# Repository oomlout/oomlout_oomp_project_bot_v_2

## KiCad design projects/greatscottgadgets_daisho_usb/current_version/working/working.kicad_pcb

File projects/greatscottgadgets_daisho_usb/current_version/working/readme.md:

# daisho
 
## summary 
* id: greatscottgadgets_daisho_usb
* user: greatscottgadgets
* name: daisho
* board: usb
* repo: https://github.com/greatscottgadgets/daisho
* src_file_repo_kicad_pcb: hw/frontend/usb/usb.kicad_pcb
* src_file_repo_kicad_pcb_link: https://github.com/greatscottgadgets/daisho/tree/master/hw/frontend/usb/usb.kicad_pcb

* src_file_repo_sch: 
* src_file_repo_sch_link: https://github.com/greatscottgadgets/daisho/tree/master/
* full details link: https://github.com/oomlout/oomlout_oomp_project_bot_v_2/tree/main/projects/greatscottgadgets_daisho_usb/current_version/working

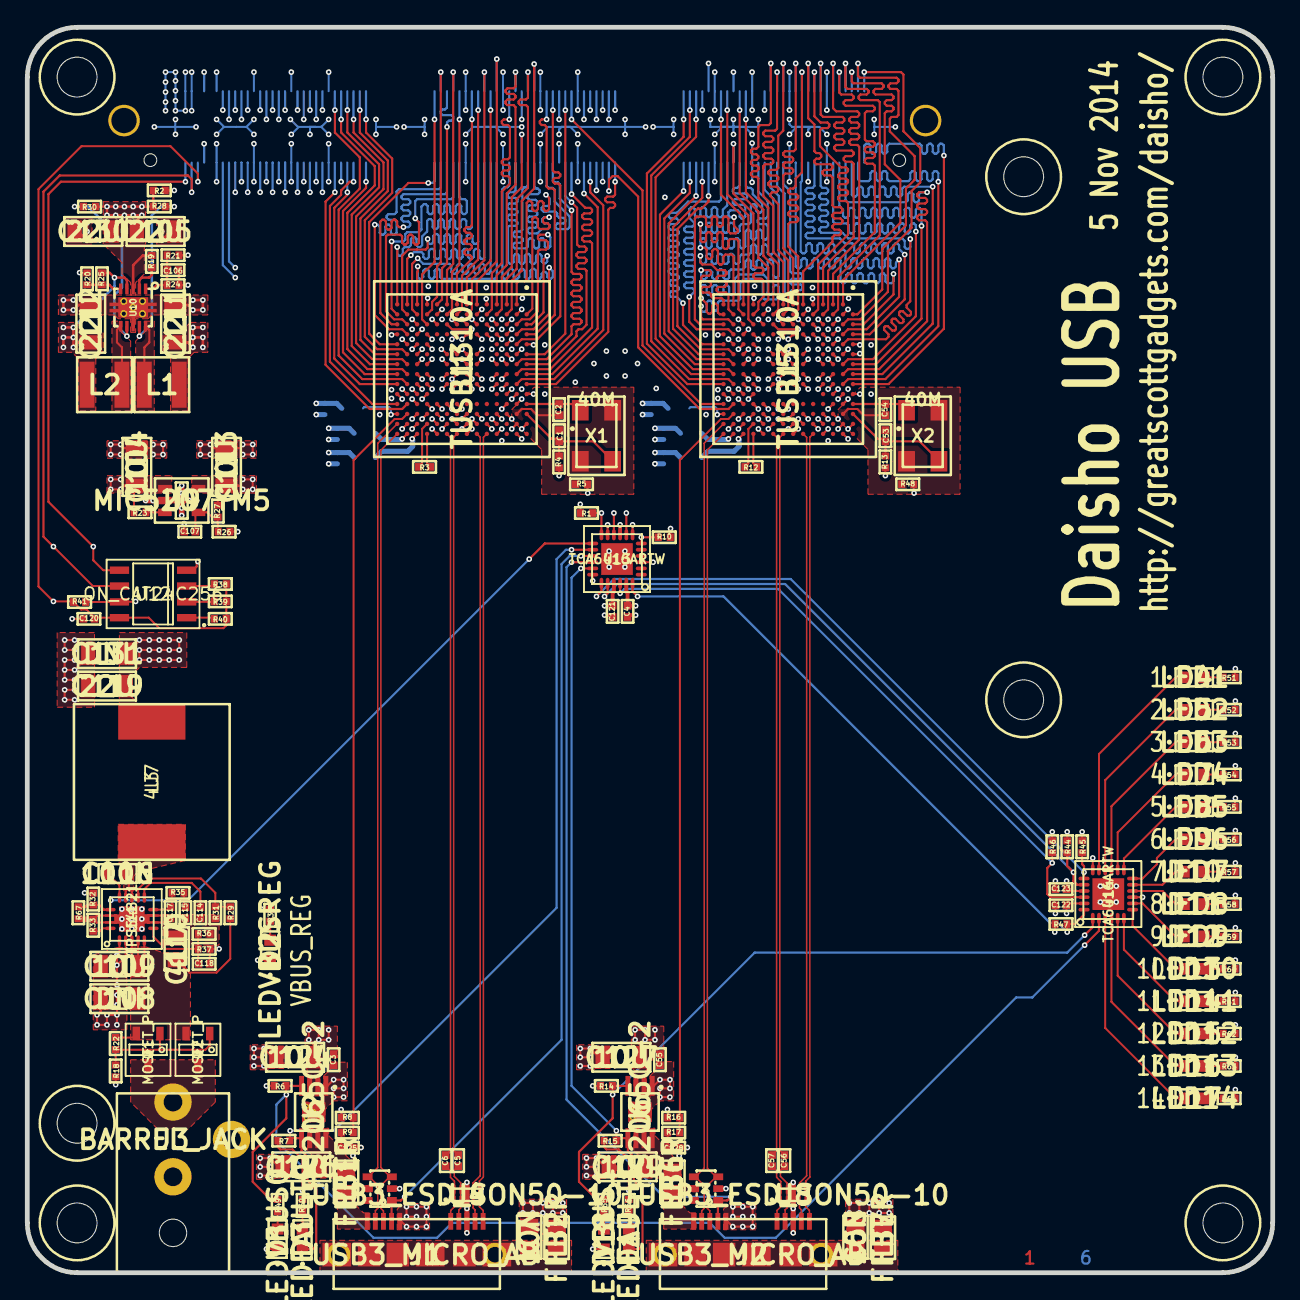
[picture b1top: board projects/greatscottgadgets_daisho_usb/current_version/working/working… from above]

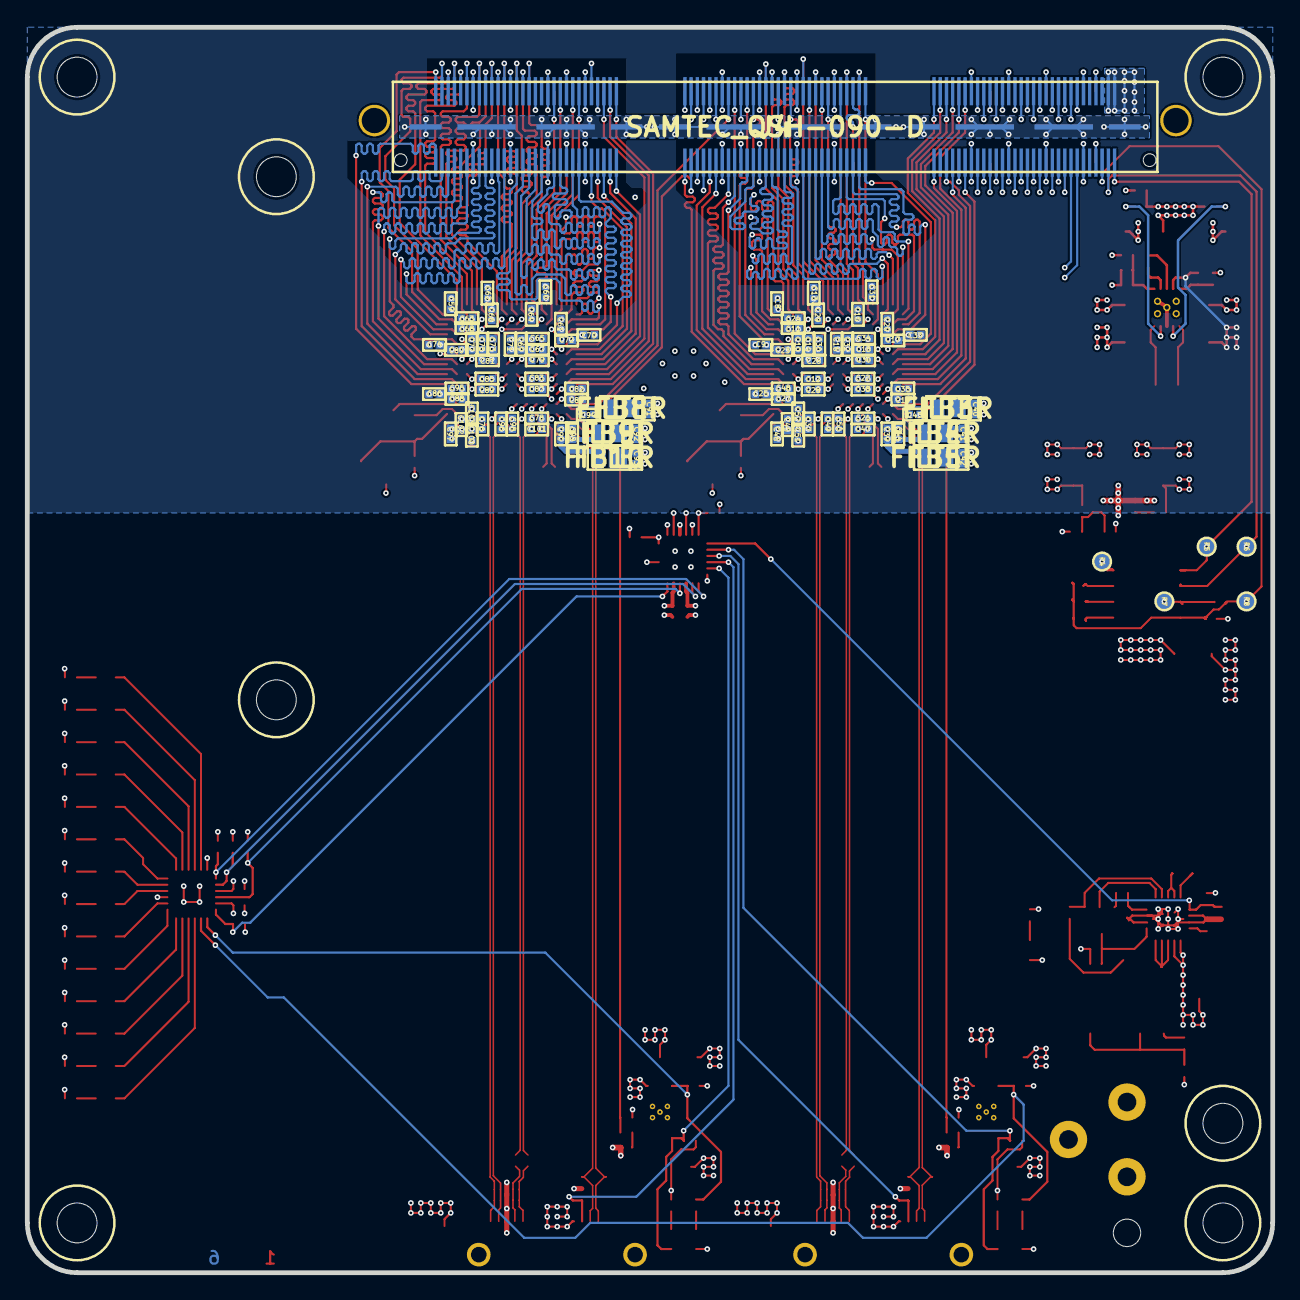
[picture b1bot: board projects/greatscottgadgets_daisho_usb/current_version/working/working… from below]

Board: 6 copper layers, 100.0 x 100.0 mm, 261 parts (109 on the bottom side), 265 nets.

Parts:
C1, C2, C53, C54: 27P; IPC_CAPC1005X55N
C3, C4, C5, C6, C8, C9, C10, C11, C12, C13, C14, C15, C16, C17, C18, C19, C20, C21, C22, C23, C24, C25, C26, C27, C28, C29, C30, C31, C32, C33, C34, C35, C36, C37, C38, C40, C41, C42, C43, C44, C45, C46, C47, C48, C49, C50, C51, C52, C55, C56, C57, C59, C60, C61, C62, C63, C64, C65, C66, C67, C68, C69, C70, C71, C72, C73, C74, C75, C76, C77, C78, C79, C80, C81, C82, C83, C84, C85, C86, C87, C88, C89, C91, C92, C93, C94, C95, C96, C97, C98, C99, C100, C101, C102, C103, C120, C121, C122, C123, C125, C128: 100N; IPC_CAPC1005X55N
C7, C58: 10N; IPC_CAPC2012X140N
C39, C90: 1U; IPC_CAPC1005X55N
C104, C109, C113, C124, C126, C127, C129: 10U; IPC_CAPC3216X180N
C105, C111, C112, C119, C130: 22U; IPC_CAPC3216X180N
C106: 33P; IPC_CAPC1005X55N
C107: 470P; IPC_CAPC1005X55N
C108, C131: DNI; IPC_CAPC3216X180N
C110: 4U7; IPC_CAPC2012X140N
C114: 22N; IPC_CAPC1005X55N
C115: 82N; IPC_CAPC1005X55N
C116: 100N; IPC_CAPC1608X90N
C117: 1N5; IPC_CAPC1005X55N
C118: 220P; IPC_CAPC1005X55N
D1: LEDVBUS0; IPC_LEDC1608X60N
D2: LEDVBUSREG; IPC_LEDC1608X60N
D3: LEDFAULT0; IPC_LEDC1608X60N
D4: LED1; IPC_LEDC1608X60N
D5: LED2; IPC_LEDC1608X60N
D6: LED3; IPC_LEDC1608X60N
D7: LED4; IPC_LEDC1608X60N
D8: LED5; IPC_LEDC1608X60N
D9: LED6; IPC_LEDC1608X60N
D10: LED7; IPC_LEDC1608X60N
D11: LED8; IPC_LEDC1608X60N
D12: LED9; IPC_LEDC1608X60N
D13: LED10; IPC_LEDC1608X60N
D14: LED11; IPC_LEDC1608X60N
D15: LED12; IPC_LEDC1608X60N
D16: LED13; IPC_LEDC1608X60N
D17: LED14; IPC_LEDC1608X60N
D18: LEDVBUS1; IPC_LEDC1608X60N
D19: LEDFAULT1; IPC_LEDC1608X60N
FB1, FB2, FB3, FB4, FB5, FB6, FB7, FB8, FB9, FB10: FILTER; IPC_INDC2012X130N
H1, H2, H4, H5, H6, H7, H8: HOLE; GSG-HOLE126MIL
J1, J2: USB3_MICRO_AB
J3: BARREL_JACK; CUI_PJ-102[AB]H
J4: SAMTEC_QSH-090-D; SAMTEC_QSH-090-01-F-D-A
L1, L2: 4U7; GSG-NRG4026
L3: 4U7; BOURNS_SRR1260
P4, P5, P6, P7, P8: CONN_1; GSG-TESTPOINT-50MIL
Q1, Q2: MOSFET_P; IPC_SOT95P280X125-3N_GSD
R1, R2, R3, R6, R7, R8, R10, R12, R14, R15, R16, R19, R44, R45, R46, R47: 10K; IPC_RESC1005X40N
R4, R5, R13, R38, R39, R40, R41, R48: DNI; IPC_RESC1005X40N
R9, R17: 90K9; IPC_RESC1005X40N
R18, R22: 30K; IPC_RESC1005X40N
R20: 165K; IPC_RESC1005X40N
R21: 180K; IPC_RESC1005X40N
R23, R28, R30: 0R; IPC_RESC1005X40N
R24: 360K; IPC_RESC1005X40N
R25: 137K; IPC_RESC1005X40N
R26: 174K; IPC_RESC1005X40N
R27: 105K; IPC_RESC1005X40N
R29: 22K; IPC_RESC1005X40N
R31: 9K53; IPC_RESC1005X40N
R32: 49K9; IPC_RESC1005X40N
R33: 52K3; IPC_RESC1005X40N
R34, R49, R50, R51, R52, R53, R54, R55, R56, R57, R58, R59, R60, R61, R62, R63, R64, R65, R66: 1K; IPC_RESC1005X40N
R35: 1K58; IPC_RESC1005X40N
R36: 2K21; IPC_RESC1005X40N
R37: 16K2; IPC_RESC1005X40N
R67: 1M; IPC_RESC1005X40N
U1, U5: TUSB1310A; IPC_BGA175C80P14X14_1200X1200X140
U2, U6: TPS2065C-2; TI_DGN_S-PDSO-G8
U3, U7: GSG-IP4220CZ6; GSG-SOT457
U4, U8: USB3_ESD_SON50-10
U9: MIC5207YM5; IPC_SOT95P280X110-5N
U10: TPS62420; TI_DRC_S-PVSON-N10
U11: TPS54821; TI_RHL_S-PVQFN-N14
U12: ON_CAT24C256; IPC_SOIC127P600X175-8N
U13, U14: TCA6416ARTW; ti_rtw_s-pwqfn-n24
X1, X2: 40M; IPC_OSCCC320X500X105-4N

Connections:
/main_board_if/EEPROM_A0: R40.1, U12.1
/main_board_if/EEPROM_A1: R39.1, U12.2
/main_board_if/EEPROM_A2: R38.1, U12.3
/main_board_if/EEPROM_VCC: C120.1, J4.6, P8.1, R38.2, R39.2, R40.2, R41.2, U12.8
/main_board_if/EEPROM_WP: P7.1, R41.1, U12.7
/main_board_if/FE_I2C_SCL: J4.4, P6.1, U12.6
/main_board_if/FE_I2C_SDA: J4.2, P5.1, U12.5
/main_board_if/IO_INT#: J4.14, R46.1, U13.22, U14.22
/main_board_if/IO_RESET#: J4.16, R47.2, U13.24, U14.24
/main_board_if/IO_SCL: J4.13, R45.1, U13.19, U14.19
/main_board_if/IO_SDA: J4.15, R44.1, U13.20, U14.20
/main_board_if/USB0_POWER_EN: R6.2, R49.2, U2.4, U14.2
/main_board_if/USB0_POWER_FLT#: D3.2, R7.2, U2.5, U13.14
/main_board_if/USB0_XI: J4.8, R4.2
/main_board_if/USB1_POWER_EN: R14.2, R65.2, U6.4, U14.1
/main_board_if/USB1_POWER_FLT#: D19.2, R15.2, U6.5, U13.17
/main_board_if/USB1_XI: J4.7, R13.2
/main_board_if/VALT_FE_PWRGD: R32.2, R67.2, U11.14, U13.13
/power/DC_IN: J3.1, Q1.D, Q2.D
/power/SW_PH: C116.2, L3.2, U11.11, U11.12
/power/SW_PVIN: C108.1, C109.1, C110.1, Q1.S, Q2.S, R22.2, R29.1, U11.4, U11.5, U11.6
/power/V1P1_FB: R20.1, R25.2, U10.5
/power/V1P1_SW: L2.1, U10.6
/power/V1P8_FB: C106.1, R21.1, R24.2, U10.1
/power/V1P8_SW: L1.2, U10.10
/usb0_interfaces/DM: J1.2, U1.P13, U3.4
/usb0_interfaces/DP: J1.3, U1.P14, U3.3
/usb0_interfaces/ELAS_BUF_MODE: J4.31, U1.C9
/usb0_interfaces/ID: J1.4, U3.1, U13.15
/usb0_interfaces/PCLK: J4.103, U1.A6
/usb0_interfaces/PHY_RESETN: U1.J3, U13.10
/usb0_interfaces/PHY_STATUS: J4.42, U1.E3
/usb0_interfaces/POWER_DOWN0: J4.46, U1.H3
/usb0_interfaces/POWER_DOWN1: J4.52, U1.G3
/usb0_interfaces/PWRPRESENT: J4.32, U1.H11
/usb0_interfaces/RESETN: R1.2, U1.J11, U13.12
/usb0_interfaces/RX_DATA0: J4.85, U1.E2
/usb0_interfaces/RX_DATA1: J4.90, U1.D2
/usb0_interfaces/RX_DATA2: J4.87, U1.D1
/usb0_interfaces/RX_DATA3: J4.91, U1.C1
/usb0_interfaces/RX_DATA4: J4.93, U1.C2
/usb0_interfaces/RX_DATA5: J4.98, U1.B1
/usb0_interfaces/RX_DATA6: J4.94, U1.A2
/usb0_interfaces/RX_DATA7: J4.88, U1.A3
/usb0_interfaces/RX_DATA8: J4.92, U1.B3
/usb0_interfaces/RX_DATA9: J4.97, U1.A4
/usb0_interfaces/RX_DATA10: J4.86, U1.B4
/usb0_interfaces/RX_DATA11: J4.99, U1.B5
/usb0_interfaces/RX_DATA12: J4.106, U1.B8
/usb0_interfaces/RX_DATA13: J4.110, U1.A8
/usb0_interfaces/RX_DATA14: J4.120, U1.A9
/usb0_interfaces/RX_DATA15: J4.112, U1.B9
/usb0_interfaces/RX_DATAK0: J4.104, U1.A7
/usb0_interfaces/RX_DATAK1: J4.100, U1.B7
/usb0_interfaces/RX_ELECIDLE: J4.17, U1.F3
/usb0_interfaces/RX_POLARITY: J4.29, U1.C8
/usb0_interfaces/RX_STATUS0: J4.21, U1.C5
/usb0_interfaces/RX_STATUS1: J4.25, U1.C6
/usb0_interfaces/RX_STATUS2: J4.27, U1.C7
/usb0_interfaces/RX_TERMINATION: J4.19, U1.D3
/usb0_interfaces/RX_VALID: J4.81, U1.F1
/usb0_interfaces/SSRXM: J1.9, U1.F14, U4.4
/usb0_interfaces/SSRXP: J1.10, U1.E14, U4.5
/usb0_interfaces/SSTXM: C6.1, U1.J14
/usb0_interfaces/SSTXM_C: C6.2, J1.6, U4.1
/usb0_interfaces/SSTXP: C5.1, U1.H14
/usb0_interfaces/SSTXP_C: C5.2, J1.7, U4.2
/usb0_interfaces/TX_CLK: J4.65, U1.K1
/usb0_interfaces/TX_DATA0: J4.62, U1.P5
/usb0_interfaces/TX_DATA1: J4.64, U1.N4
/usb0_interfaces/TX_DATA2: J4.66, U1.P3
/usb0_interfaces/TX_DATA3: J4.68, U1.N3
/usb0_interfaces/TX_DATA4: J4.70, U1.P2
/usb0_interfaces/TX_DATA5: J4.76, U1.N2
/usb0_interfaces/TX_DATA6: J4.74, U1.P1
/usb0_interfaces/TX_DATA7: J4.78, U1.N1
/usb0_interfaces/TX_DATA8: J4.82, U1.M1
/usb0_interfaces/TX_DATA9: J4.80, U1.M2
/usb0_interfaces/TX_DATA10: J4.63, U1.L2
/usb0_interfaces/TX_DATA11: J4.61, U1.L3
/usb0_interfaces/TX_DATA12: J4.69, U1.J2
/usb0_interfaces/TX_DATA13: J4.73, U1.H1
/usb0_interfaces/TX_DATA14: J4.75, U1.H2
/usb0_interfaces/TX_DATA15: J4.79, U1.G2
/usb0_interfaces/TX_DATAK0: J4.67, U1.J1
/usb0_interfaces/TX_DATAK1: J4.77, U1.G1
/usb0_interfaces/TX_DEEMPH0: J4.28, U1.L11
/usb0_interfaces/TX_DEEMPH1: J4.30, U1.K11
/usb0_interfaces/TX_DETRX_LPBK: J4.38, U1.M6
/usb0_interfaces/TX_ELECIDLE: J4.44, U1.K3
/usb0_interfaces/TX_MARGIN0: J4.22, U1.M9
/usb0_interfaces/TX_MARGIN1: J4.20, U1.M10
/usb0_interfaces/TX_MARGIN2: J4.18, U1.M11
/usb0_interfaces/TX_ONESZEROS: U1.M4, U13.11
/usb0_interfaces/TX_SWING: J4.40, U1.M5
/usb0_interfaces/ULPI_CLK: J4.56, U1.P11
/usb0_interfaces/ULPI_DATA0: J4.49, U1.N9
/usb0_interfaces/ULPI_DATA1: J4.54, U1.P9
/usb0_interfaces/ULPI_DATA2: J4.60, U1.P8
/usb0_interfaces/ULPI_DATA3: J4.51, U1.N8
/usb0_interfaces/ULPI_DATA4: J4.53, U1.P7
/usb0_interfaces/ULPI_DATA5: J4.55, U1.N7
/usb0_interfaces/ULPI_DATA6: J4.57, U1.P6
/usb0_interfaces/ULPI_DATA7: J4.59, U1.N6
/usb0_interfaces/ULPI_DIR: J4.34, U1.M7
/usb0_interfaces/ULPI_NXT: J4.50, U1.N11
/usb0_interfaces/ULPI_STP: J4.26, U1.M8
/usb0_interfaces/USB3_SHIELD: C7.1, FB2.2, J1.11
/usb0_interfaces/VBUS: C125.1, C126.1, FB1.1, R9.2, U2.6, U2.7, U2.8
/usb0_interfaces/VBUS_RAW: FB1.2, J1.1, U3.5
/usb0_interfaces/VSSOSC: C1.2, C2.2, R5.2, U1.B12, X1.2, X1.4
/usb0_interfaces/XI: C1.1, R4.1, U1.A12, X1.3
/usb0_interfaces/XO: C2.1, U1.A11, X1.1
/usb0_power/A1P1: C39.1, C45.1, C47.1, C49.1, C50.1, C51.1, C52.1, FB5.2, U1.C11, U1.C12, U1.D14, U1.G13, U1.G14, U1.K14, U1.M14
/usb0_power/A1P8: C44.1, C46.1, C48.1, FB4.2, U1.A13, U1.C10, U1.N14
/usb0_power/A3P3: C43.1, FB3.2, U1.P12
/usb1_interfaces/DM: J2.2, U5.P13, U7.4
/usb1_interfaces/DP: J2.3, U5.P14, U7.3
/usb1_interfaces/ELAS_BUF_MODE: J4.137, U5.C9
/usb1_interfaces/ID: J2.4, U7.1, U13.16
/usb1_interfaces/PCLK: J4.147, U5.A6
/usb1_interfaces/PHY_RESETN: U5.J3, U13.7
/usb1_interfaces/PHY_STATUS: J4.101, U5.E3
/usb1_interfaces/POWER_DOWN0: J4.111, U5.H3
/usb1_interfaces/POWER_DOWN1: J4.113, U5.G3
/usb1_interfaces/PWRPRESENT: J4.114, U5.H11
/usb1_interfaces/RESETN: R10.2, U5.J11, U13.6
/usb1_interfaces/RX_DATA0: J4.163, U5.E2
/usb1_interfaces/RX_DATA1: J4.169, U5.D2
/usb1_interfaces/RX_DATA2: J4.165, U5.D1
/usb1_interfaces/RX_DATA3: J4.171, U5.C1
/usb1_interfaces/RX_DATA4: J4.173, U5.C2
/usb1_interfaces/RX_DATA5: J4.175, U5.B1
/usb1_interfaces/RX_DATA6: J4.177, U5.A2
/usb1_interfaces/RX_DATA7: J4.158, U5.A3
/usb1_interfaces/RX_DATA8: J4.179, U5.B3
/usb1_interfaces/RX_DATA9: J4.164, U5.A4
/usb1_interfaces/RX_DATA10: J4.160, U5.B4
/usb1_interfaces/RX_DATA11: J4.166, U5.B5
/usb1_interfaces/RX_DATA12: J4.174, U5.B8
/usb1_interfaces/RX_DATA13: J4.176, U5.A8
/usb1_interfaces/RX_DATA14: J4.180, U5.A9
/usb1_interfaces/RX_DATA15: J4.178, U5.B9
/usb1_interfaces/RX_DATAK0: J4.172, U5.A7
/usb1_interfaces/RX_DATAK1: J4.170, U5.B7
/usb1_interfaces/RX_ELECIDLE: J4.115, U5.F3
/usb1_interfaces/RX_POLARITY: J4.129, U5.C8
/usb1_interfaces/RX_STATUS0: J4.119, U5.C5
/usb1_interfaces/RX_STATUS1: J4.127, U5.C6
/usb1_interfaces/RX_STATUS2: J4.162, U5.C7
/usb1_interfaces/RX_TERMINATION: J4.117, U5.D3
/usb1_interfaces/RX_VALID: J4.161, U5.F1
/usb1_interfaces/SSRXM: J2.9, U5.F14, U8.4
/usb1_interfaces/SSRXP: J2.10, U5.E14, U8.5
/usb1_interfaces/SSTXM: C57.1, U5.J14
/usb1_interfaces/SSTXM_C: C57.2, J2.6, U8.1
/usb1_interfaces/SSTXP: C56.1, U5.H14
/usb1_interfaces/SSTXP_C: C56.2, J2.7, U8.2
/usb1_interfaces/TX_CLK: J4.139, U5.K1
/usb1_interfaces/TX_DATA0: J4.134, U5.P5
/usb1_interfaces/TX_DATA1: J4.136, U5.N4
/usb1_interfaces/TX_DATA2: J4.140, U5.P3
/usb1_interfaces/TX_DATA3: J4.154, U5.N3
/usb1_interfaces/TX_DATA4: J4.152, U5.P2
/usb1_interfaces/TX_DATA5: J4.148, U5.N2
/usb1_interfaces/TX_DATA6: J4.150, U5.P1
/usb1_interfaces/TX_DATA7: J4.146, U5.N1
/usb1_interfaces/TX_DATA8: J4.133, U5.M1
/usb1_interfaces/TX_DATA9: J4.142, U5.M2
/usb1_interfaces/TX_DATA10: J4.138, U5.L2
/usb1_interfaces/TX_DATA11: J4.135, U5.L3
/usb1_interfaces/TX_DATA12: J4.149, U5.J2
/usb1_interfaces/TX_DATA13: J4.151, U5.H1
/usb1_interfaces/TX_DATA14: J4.153, U5.H2
/usb1_interfaces/TX_DATA15: J4.159, U5.G2
/usb1_interfaces/TX_DATAK0: J4.141, U5.J1
/usb1_interfaces/TX_DATAK1: J4.157, U5.G1
/usb1_interfaces/TX_DEEMPH0: J4.37, U5.L11
/usb1_interfaces/TX_DEEMPH1: J4.33, U5.K11
/usb1_interfaces/TX_DETRX_LPBK: J4.89, U5.M6
/usb1_interfaces/TX_ELECIDLE: J4.109, U5.K3
/usb1_interfaces/TX_MARGIN0: J4.41, U5.M9
/usb1_interfaces/TX_MARGIN1: J4.43, U5.M10
/usb1_interfaces/TX_MARGIN2: J4.45, U5.M11
/usb1_interfaces/TX_ONESZEROS: U5.M4, U13.8
/usb1_interfaces/TX_SWING: J4.102, U5.M5
/usb1_interfaces/ULPI_CLK: J4.105, U5.P11
/usb1_interfaces/ULPI_DATA0: J4.123, U5.N9
/usb1_interfaces/ULPI_DATA1: J4.121, U5.P9
/usb1_interfaces/ULPI_DATA2: J4.125, U5.P8
/usb1_interfaces/ULPI_DATA3: J4.122, U5.N8
/usb1_interfaces/ULPI_DATA4: J4.124, U5.P7
/usb1_interfaces/ULPI_DATA5: J4.126, U5.N7
/usb1_interfaces/ULPI_DATA6: J4.128, U5.P6
/usb1_interfaces/ULPI_DATA7: J4.130, U5.N6
/usb1_interfaces/ULPI_DIR: J4.116, U5.M7
/usb1_interfaces/ULPI_NXT: J4.118, U5.N11
/usb1_interfaces/ULPI_STP: J4.39, U5.M8
/usb1_interfaces/USB3_SHIELD: C58.1, FB7.2, J2.11
/usb1_interfaces/VBUS: C128.1, C129.1, FB6.1, R17.2, U6.6, U6.7, U6.8
/usb1_interfaces/VBUS_RAW: FB6.2, J2.1, U7.5
/usb1_interfaces/VSSOSC: C53.2, C54.2, R48.2, U5.B12, X2.2, X2.4
/usb1_interfaces/XI: C53.1, R13.1, U5.A12, X2.3
/usb1_interfaces/XO: C54.1, U5.A11, X2.1
/usb1_power/A1P1: C90.1, C96.1, C98.1, C100.1, C101.1, C102.1, C103.1, FB10.2, U5.C11, U5.C12, U5.D14, U5.G13, U5.G14, U5.K14, U5.M14
/usb1_power/A1P8: C95.1, C97.1, C99.1, FB9.2, U5.A13, U5.C10, U5.N14
/usb1_power/A3P3: C94.1, FB8.2, U5.P12
GND: C3.2, C4.2, C7.2, C8.2, C9.2, C10.2, C11.2, C12.2, C13.2, C14.2, C15.2, C16.2, C17.2, C18.2, C19.2, C20.2, C21.2, C22.2, C23.2, C24.2, C25.2, C26.2, C27.2, C28.2, C29.2, C30.2, C31.2, C32.2, C33.2, C34.2, C35.2, C36.2, C37.2, C38.2, C39.2, C40.2, C41.2, C42.2, C43.2, C44.2, C45.2, C46.2, C47.2, C48.2, C49.2, C50.2, C51.2, C52.2, C55.2, C58.2, C59.2, C60.2, C61.2, C62.2, C63.2, C64.2, C65.2, C66.2, C67.2, C68.2, C69.2, C70.2, C71.2, C72.2, C73.2, C74.2, C75.2, C76.2, C77.2, C78.2, C79.2, C80.2, C81.2, C82.2, C83.2, C84.2, C85.2, C86.2, C87.2, C88.2, C89.2, C90.2, C91.2, C92.2, C93.2, C94.2, C95.2, C96.2, C97.2, C98.2, C99.2, C100.2, C101.2, C102.2, C103.2, C104.2, C105.2, C107.2, C108.2, C109.2, C110.2, C111.2, C112.1, C113.2, C114.2, C115.2, C117.2, C119.2, C120.2, C121.2, C122.2, C123.2, C124.2, C125.2, C126.2, C127.2, C128.2, C129.2, C130.2, C131.2, D1.2, D2.2, D18.2, FB2.1, FB7.1, J1.5, J1.8, J2.5, J2.8, J3.2, J4.A0, J4.A1, J4.A2, J4.A3, J4.B0, J4.B1, J4.B2, J4.B3, J4.C0, J4.C1, J4.C2, J4.C3, P4.1, R1.1, R5.1, R6.1, R8.2, R10.1, R14.1, R16.2, R18.1, R20.2, R21.2, R26.2, R31.1, R33.1, R36.1, R47.1, R48.1, R67.1, U1.B11, U1.B13, U1.B14, U1.D12, U1.E13, U1.F6, U1.F7, U1.F8, U1.F9, U1.F12, U1.F13, U1.G6, U1.G7, U1.G8, U1.G9, U1.G12, U1.H6, U1.H7, U1.H8, U1.H9, U1.H13, U1.J6, U1.J7, U1.J8, U1.J9, U1.J13, U1.K12, U1.L12, U1.M12, U1.M13, U1.N13, U2.1, U2.9, U3.2, U4.3, U5.B11, U5.B13, U5.B14, U5.D12, U5.E13, U5.F6, U5.F7, U5.F8, U5.F9, U5.F12, U5.F13, U5.G6, U5.G7, U5.G8, U5.G9, U5.G12, U5.H6, U5.H7, U5.H8, U5.H9, U5.H13, U5.J6, U5.J7, U5.J8, U5.J9, U5.J13, U5.K12, U5.L12, U5.M12, U5.M13, U5.N13, U6.1, U6.9, U7.2, U8.3, U9.2, U10.0, U10.8, U11.2, U11.3, U11.15, U12.4, U13.9, U13.18, U13.25, U14.9, U14.25
unnamed: C107.1, R26.1, R27.2, U9.4
unnamed: C114.1, U11.9
unnamed: C115.1, R35.1
unnamed: C116.1, U11.13
unnamed: C117.1, R35.2, U11.8
unnamed: C118.2, R36.2, R37.1, U11.7
unnamed: D1.1, R49.1
unnamed: D2.1, R34.1
unnamed: D3.1, R50.2
unnamed: D4.1, R51.1
unnamed: D4.2, U14.17
unnamed: D5.1, R52.1
unnamed: D5.2, U14.16
unnamed: D6.1, R53.1
unnamed: D6.2, U14.15
unnamed: D7.1, R54.1
unnamed: D7.2, U14.14
unnamed: D8.1, R55.1
unnamed: D8.2, U14.13
unnamed: D9.1, R56.1
unnamed: D9.2, U14.12
unnamed: D10.1, R57.1
unnamed: D10.2, U14.11
unnamed: D11.1, R58.1
unnamed: D11.2, U14.10
unnamed: D12.1, R59.1
unnamed: D12.2, U14.8
unnamed: D13.1, R60.1
unnamed: D13.2, U14.7
unnamed: D14.1, R61.1
unnamed: D14.2, U14.6
unnamed: D15.1, R62.1
unnamed: D15.2, U14.5
unnamed: D16.1, R63.1
unnamed: D16.2, U14.4
unnamed: D17.1, R64.1
unnamed: D17.2, U14.3
unnamed: D18.1, R65.1
unnamed: D19.1, R66.2
unnamed: Q1.G, Q2.G, R18.2, R22.1
unnamed: R3.1, U1.L13
unnamed: R3.2, U1.L14
unnamed: R8.1, R9.1, U1.N12
unnamed: R12.1, U5.L13
unnamed: R12.2, U5.L14
unnamed: R16.1, R17.1, U5.N12
unnamed: R19.2, U10.2
unnamed: R23.2, U9.3
unnamed: R28.1, U10.9
unnamed: R29.2, R31.2, U11.10
unnamed: R30.1, U10.7
unnamed: R33.2, U11.1
V1P1: C9.1, C11.1, C13.1, C15.1, C17.1, C19.1, C21.1, C23.1, C25.1, C27.1, C29.1, C31.1, C33.1, C35.1, C37.1, C42.1, C60.1, C62.1, C64.1, C66.1, C68.1, C70.1, C72.1, C74.1, C76.1, C78.1, C80.1, C82.1, C84.1, C86.1, C88.1, C93.1, C112.2, FB5.1, FB10.1, L2.2, R25.1, U1.A5, U1.A10, U1.B6, U1.B10, U1.C4, U1.D13, U1.E1, U1.F2, U1.K2, U1.K13, U1.L1, U1.N5, U1.N10, U1.P4, U1.P10, U5.A5, U5.A10, U5.B6, U5.B10, U5.C4, U5.D13, U5.E1, U5.F2, U5.K2, U5.K13, U5.L1, U5.N5, U5.N10, U5.P4, U5.P10, U10.4
V1P8: C4.1, C8.1, C10.1, C12.1, C14.1, C16.1, C18.1, C20.1, C22.1, C24.1, C26.1, C28.1, C30.1, C32.1, C34.1, C36.1, C38.1, C41.1, C59.1, C61.1, C63.1, C65.1, C67.1, C69.1, C71.1, C73.1, C75.1, C77.1, C79.1, C81.1, C83.1, C85.1, C87.1, C89.1, C92.1, C106.2, C111.1, C121.1, C122.1, FB4.1, FB9.1, J4.12, J4.24, J4.36, J4.48, J4.71, J4.72, J4.83, J4.84, J4.95, J4.96, J4.107, J4.108, J4.131, J4.132, J4.143, J4.144, J4.155, J4.156, J4.167, J4.168, L1.1, R24.1, R44.2, R45.2, R46.2, U1.B2, U1.C3, U1.D4, U1.D7, U1.D8, U1.D9, U1.E4, U1.F4, U1.G4, U1.H4, U1.L4, U1.L5, U1.L7, U1.L8, U1.L9, U1.L10, U1.M3, U5.B2, U5.C3, U5.D4, U5.D7, U5.D8, U5.D9, U5.E4, U5.F4, U5.G4, U5.H4, U5.L4, U5.L5, U5.L7, U5.L8, U5.L9, U5.L10, U5.M3, U13.21, U13.23, U14.23
V3P3D: C40.1, C91.1, C113.1, FB3.1, FB8.1, R27.1, U9.5
VBUS_REG: C3.1, C55.1, C118.1, C119.1, C124.1, C127.1, C131.1, J4.1, J4.3, L3.1, R2.2, R34.2, R37.2, U2.2, U2.3, U6.2, U6.3, U13.3
VRAW_SW: C104.1, C105.1, C123.1, C130.1, J4.11, J4.23, J4.35, J4.47, R2.1, R7.1, R15.1, R19.1, R23.1, R28.2, R30.2, R32.1, R50.1, R51.2, R52.2, R53.2, R54.2, R55.2, R56.2, R57.2, R58.2, R59.2, R60.2, R61.2, R62.2, R63.2, R64.2, R66.1, U9.1, U10.3, U14.18, U14.21

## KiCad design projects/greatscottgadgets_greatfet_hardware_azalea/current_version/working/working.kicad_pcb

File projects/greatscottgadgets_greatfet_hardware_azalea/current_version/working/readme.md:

# greatfet_hardware
 
## summary 
* id: greatscottgadgets_greatfet_hardware_azalea
* user: greatscottgadgets
* name: greatfet_hardware
* board: azalea
* repo: https://github.com/greatscottgadgets/greatfet-hardware
* src_file_repo_kicad_pcb: azalea/azalea.kicad_pcb
* src_file_repo_kicad_pcb_link: https://github.com/greatscottgadgets/greatfet-hardware/tree/master/azalea/azalea.kicad_pcb

* src_file_repo_sch: azalea/azalea.sch
* src_file_repo_sch_link: https://github.com/greatscottgadgets/greatfet-hardware/tree/master/azalea/azalea.sch
* full details link: https://github.com/oomlout/oomlout_oomp_project_bot_v_2/tree/main/projects/greatscottgadgets_greatfet_hardware_azalea/current_version/working

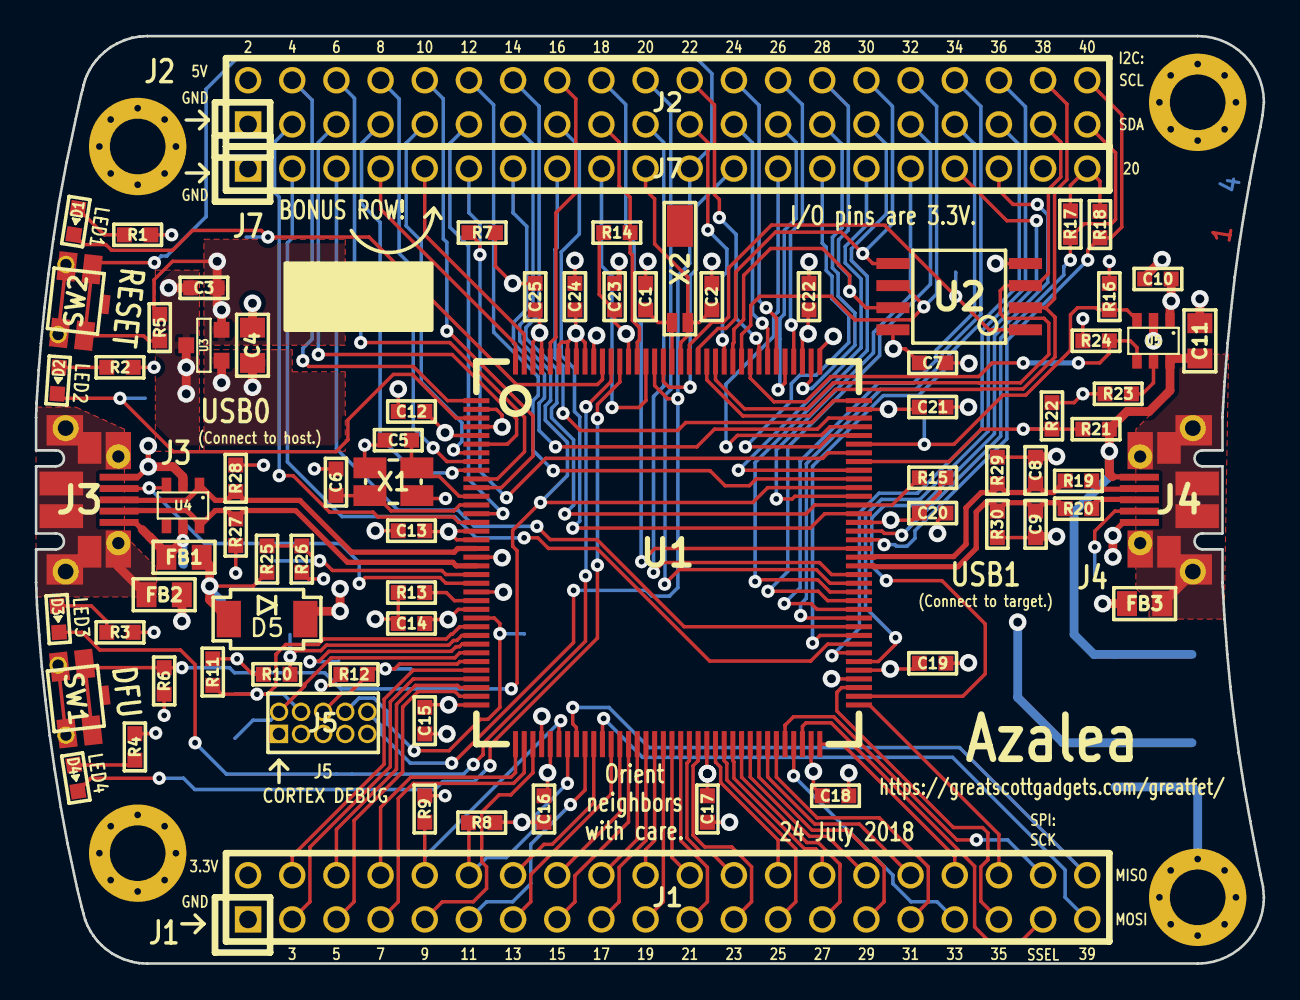
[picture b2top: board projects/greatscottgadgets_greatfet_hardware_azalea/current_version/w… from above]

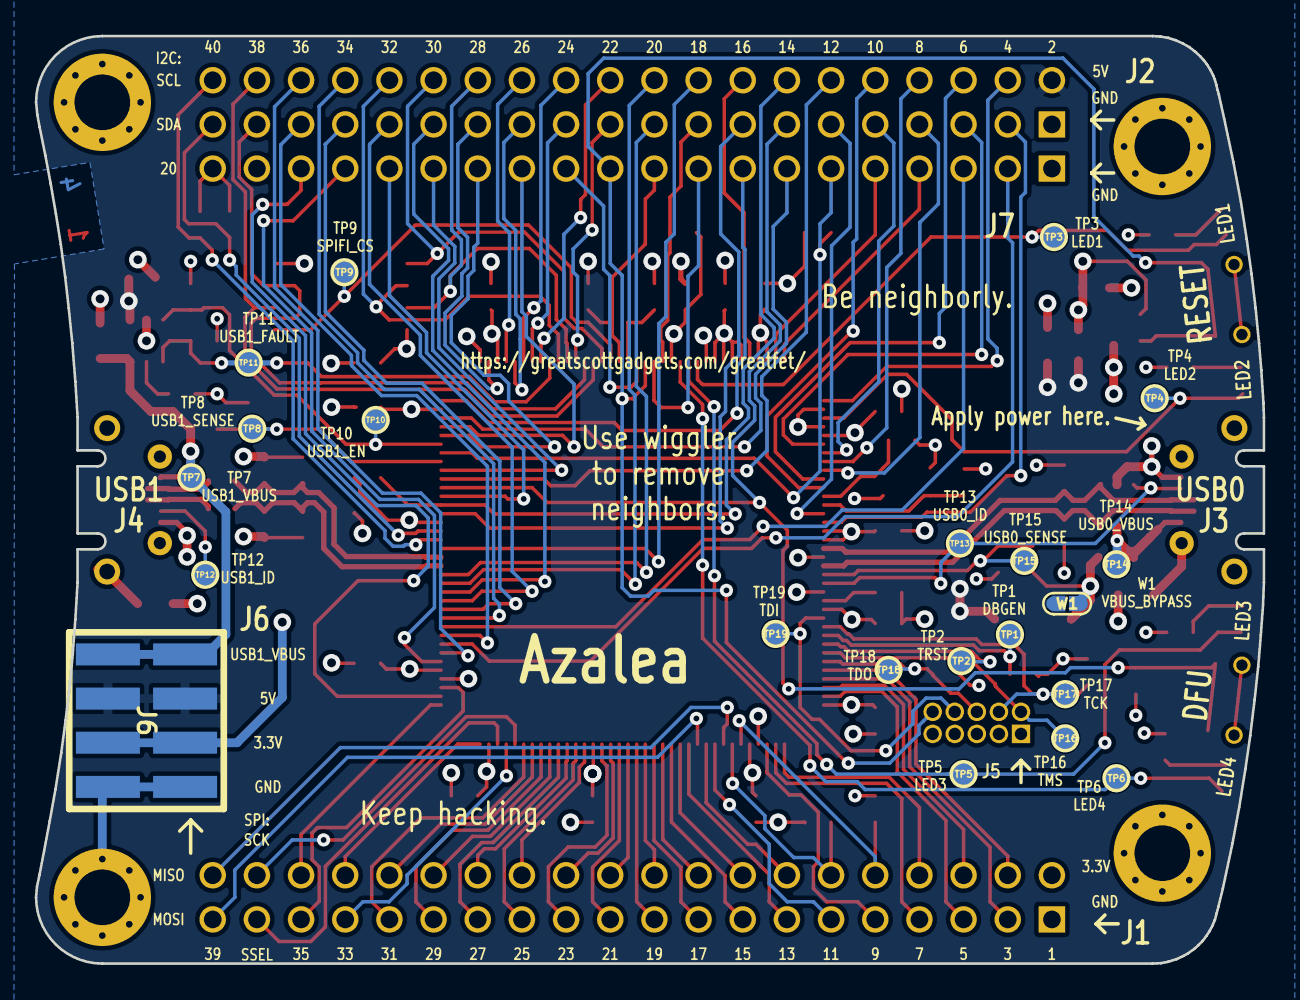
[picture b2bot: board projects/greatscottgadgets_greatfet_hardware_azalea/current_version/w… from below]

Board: 4 copper layers, 70.6 x 53.3 mm, 103 parts (21 on the bottom side), 133 nets.

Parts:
C1, C2, C5, C6, C8, C9: 18pF; 0603
C3, C10: 1uF; 0603
C4, C11: 10uF; 0805
C7, C12, C13, C14, C15, C16, C17, C18, C19, C20, C21, C22, C23, C24, C25: 100nF; 0603
D1: LED1; 0603D
D2: LED2; 0603D
D3: LED3; 0603D
D4: LED4; 0603D
D5: VBUS_DIODE; SOD128
FB1, FB2, FB3: FILTER; 0805
J1: NEIGHBOR1; HEADER-2x20
J2: NEIGHBOR2; HEADER-2x20
J3, J4: USB-MICRO-B-SHIELDED; USB-MICROB-FCI-10103592-LONGPADS
J5: JTAG; 50MIL-HEADER-2x5-TH
J6: POWER; HEADER-SMT-2x4
J7: BONUS_ROW; HEADER-1x20
MH1, MH2, MH3, MH4: MOUNTING_HOLE; HOLE126MIL-COPPER
R1, R2, R3, R4: 330; 0603
R5, R6, R7, R8, R9, R10, R11, R12, R14, R15, R16, R21, R24, R25: 10k; 0603
R13: 12.0k; 0603
R17, R18: 1.8k; 0603
R19, R20: 33.0; 0603
R22, R26: 18k; 0603
R23: 43.2k; 0603
R27, R28, R29, R30: 15k; 0603
SW1: DFU; SWITCH-PTS840-P
SW2: RESET; SWITCH-PTS840-P
TP1: DBGEN; TESTPOINT-50MIL
TP2: TRST; TESTPOINT-50MIL
TP3: LED1; TESTPOINT-50MIL
TP4: LED2; TESTPOINT-50MIL
TP5: LED3; TESTPOINT-50MIL
TP6: LED4; TESTPOINT-50MIL
TP7: USB1_VBUS; TESTPOINT-50MIL
TP8: USB1_SENSE; TESTPOINT-50MIL
TP9: SPIFI_CS; TESTPOINT-50MIL
TP10: USB1_EN; TESTPOINT-50MIL
TP11: USB1_FAULT; TESTPOINT-50MIL
TP12: USB1_ID; TESTPOINT-50MIL
TP13: USB0_ID; TESTPOINT-50MIL
TP14: USB0_VBUS; TESTPOINT-50MIL
TP15: USB0_SENSE; TESTPOINT-50MIL
TP16: TMS; TESTPOINT-50MIL
TP17: TCK; TESTPOINT-50MIL
TP18: TDO; TESTPOINT-50MIL
TP19: TDI; TESTPOINT-50MIL
U1: LPC4330FBD144; LQFP144
U2: W25Q16DV; SOIC8-208
U3: AP7333; SOT23-3
U4: IP4220CZ6; SOT457
U5: AP2553W6-7; SOT457
W1: VBUS_BYPASS; 0603-JUMPER
X1: MCU_XTAL; XTAL3.2x2.5mm-EXT
X2: RTC_XTAL; XTAL-AB26TRQ

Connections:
+5V: C4.1, C10.1, D5.1, J2.2, J6.5, J6.6, U3.1, U5.1, W1.1
/ADC0_0: J2.5, U1.6
/ADC0_2: J7.5, U1.143
/ADC0_5: J7.4, U1.144
/CLK0: J1.11, U1.45
/CLK2: J2.12, U1.99
/DBGEN: R10.2, TP1.1, U1.28
/I2C0_SCL: J2.40, R18.2, U1.92
/I2C0_SDA: J2.39, R17.2, U1.93
/LED1: D1.1, TP3.1, U1.134
/LED2: D2.1, TP4.1, U1.3
/LED3: D3.1, TP5.1, U1.133
/LED4: D4.1, TP6.1, U1.132
/P0_0: J1.4, U1.32
/P0_1: J1.6, U1.34
/P1_0: J1.7, U1.38
/P1_1: J1.10, R9.2, U1.42
/P1_2: J1.12, R8.1, U1.43
/P1_3: J1.40, U1.44
/P1_4: J1.39, U1.47
/P1_5: J1.13, U1.48
/P1_6: J1.16, U1.49
/P1_7: J1.15, U1.50
/P1_8: J1.18, U1.51
/P1_9: J1.17, U1.52
/P1_10: J1.20, U1.53
/P1_11: J1.22, U1.55
/P1_12: J1.21, U1.56
/P1_13: J1.26, U1.60
/P1_14: J1.25, U1.61
/P1_15: J1.28, U1.62
/P1_16: J1.30, U1.64
/P1_17: J1.32, U1.66
/P1_18: J1.31, U1.67
/P1_19: J1.38, U1.68
/P1_20: J1.37, U1.70
/P2_0: J1.35, U1.75
/P2_1: J2.35, U1.81
/P2_2: J2.33, U1.84
/P2_3: J2.20, U1.87
/P2_4: J2.19, U1.88
/P2_5: J2.18, U1.91
/P2_6: J2.15, U1.95
/P2_7: J2.14, R15.2, U1.96
/P2_8: J2.13, R6.1, SW1.1, U1.98
/P2_9: J7.6, R7.1, U1.102
/P2_10: J7.14, U1.104
/P2_11: J7.13, U1.105
/P2_12: J7.7, U1.106
/P2_13: J7.8, U1.108
/P3_0: J2.26, U1.112
/P3_1: J2.24, U1.114
/P3_2: J2.22, U1.116
/P3_3: J2.32, U1.118, U2.6
/P3_4: J2.28, U1.119, U2.7
/P3_5: J2.37, U1.121, U2.3
/P3_6: J2.38, U1.122, U2.2
/P3_7: J2.30, U1.123, U2.5
/P4_0: J2.4, U1.1
/P4_2: J2.8, U1.8
/P4_3: J2.9, U1.7
/P4_4: J2.7, U1.9
/P4_5: J2.6, U1.10
/P4_6: J2.10, U1.11
/P4_7: J2.11, U1.14
/P4_8: J2.3, U1.15
/P4_9: J1.3, U1.33
/P4_10: J1.5, U1.35
/P5_0: J1.8, U1.37
/P5_1: J1.9, U1.39
/P5_2: J1.14, U1.46
/P5_3: J1.19, U1.54
/P5_4: J1.24, U1.57
/P5_5: J1.23, U1.58
/P5_6: J1.27, U1.63
/P5_7: J1.29, U1.65
/P6_0: J1.36, U1.73
/P6_1: J7.18, U1.74
/P6_2: J7.17, U1.78
/P6_3: J2.36, U1.79
/P6_4: J7.2, U1.80
/P6_5: J7.3, U1.82
/P6_6: J2.34, U1.83
/P6_7: J2.31, U1.85
/P6_8: J2.29, U1.86
/P6_9: J7.16, U1.97
/P6_10: J7.15, U1.100
/P7_0: J2.27, U1.110
/P7_1: J2.25, U1.113
/P7_2: J2.23, U1.115
/P7_7: J2.16, U1.140
/P9_5: J1.33, U1.69
/P9_6: J1.34, U1.72
/PF_4: J2.21, U1.120
/RESET: J5.10, J7.11, R5.2, SW2.1, U1.128
/RTCX1: C2.1, J7.10, U1.125, X2.2
/RTCX2: C1.1, U1.126, X2.1
/RTC_ALARM: J7.9, U1.129
/SPIFI_CS: TP9.1, U1.124, U2.1
/TCK: J5.4, R11.2, TP17.1, U1.27
/TDI: J5.8, TP19.1, U1.26
/TDO: J5.6, R12.2, TP18.1, U1.31
/TMS: J5.2, TP16.1, U1.30
/TRST: TP2.1, U1.29
/USB0_D+: J3.3, R28.1, U1.18, U4.1
/USB0_D-: J3.2, R27.1, U1.20, U4.6
/USB0_ID: J3.4, TP13.1, U1.22, U4.3
/USB0_SENSE: R25.2, R26.2, TP15.1, U1.21
/USB0_SHIELD: FB2.2, J3.0
/USB0_VBUS: FB1.1, J3.1, TP14.1, U4.5
/USB1_D+: C9.1, R20.2, R30.1, U1.89
/USB1_D-: C8.1, R19.2, R29.1, U1.90
/USB1_EN: R16.2, TP10.1, U1.103, U5.3
/USB1_FAULT: R24.1, TP11.1, U1.117, U5.4
/USB1_ID: J4.4, TP12.1
/USB1_SENSE: R21.2, R22.2, TP8.1, U1.101
/USB1_SHIELD: FB3.1, J4.0
/USB1_VBUS: C11.1, J4.1, J6.7, J6.8, R21.1, TP7.1, U5.6
/VBAT: J7.12, U1.127
/WAKEUP0: J2.17, R14.2, U1.130
GND: C1.2, C2.2, C3.2, C4.2, C5.2, C6.2, C7.2, C8.2, C9.2, C10.2, C11.2, C12.2, C13.2, C14.2, C15.2, C16.2, C17.2, C18.2, C19.2, C20.2, C21.2, C22.2, C23.2, C24.2, C25.2, FB2.1, FB3.2, J1.1, J2.1, J3.5, J4.5, J5.3, J5.5, J5.9, J6.1, J6.2, J7.1, J7.19, MH1.1, MH2.1, MH3.1, MH4.1, R6.2, R7.2, R8.2, R13.2, R16.1, R22.1, R23.1, R26.1, R27.2, R28.2, R29.2, R30.2, SW2.2, U1.2, U1.4, U1.19, U1.23, U1.40, U1.76, U1.109, U1.135, U2.4, U3.3, U4.2, U5.2, X1.2, X1.4
unnamed: C5.1, U1.12, X1.1
unnamed: C6.1, U1.13, X1.3
unnamed: D1.2, R1.2
unnamed: D2.2, R2.2
unnamed: D3.2, R3.2
unnamed: D4.2, R4.2
unnamed: D5.2, FB1.2, R25.1, W1.2
unnamed: J4.2, R19.1
unnamed: J4.3, R20.1
unnamed: R13.1, U1.24
unnamed: R23.2, U5.5
VCC: C3.1, C7.1, C12.1, C13.1, C14.1, C15.1, C16.1, C17.1, C18.1, C19.1, C20.1, C21.1, C22.1, C23.1, C24.1, C25.1, J1.2, J5.1, J6.3, J6.4, J7.20, R1.1, R2.1, R3.1, R4.1, R5.1, R9.1, R10.1, R11.1, R12.1, R14.1, R15.1, R17.1, R18.1, R24.2, SW1.2, U1.5, U1.16, U1.17, U1.25, U1.36, U1.41, U1.59, U1.71, U1.77, U1.94, U1.107, U1.111, U1.131, U1.136, U1.137, U1.138, U1.139, U1.141, U1.142, U2.8, U3.2

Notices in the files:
projects/greatscottgadgets_greatfet_hardware_azalea/current_version/working/working.kicad_pcb:
Copyright 2015-2018 Great Scott Gadgets
License: BSD-3-Clause
projects/greatscottgadgets_greatfet_hardware_azalea/current_version/working/working.kicad_sch:
Copyright © 2013 Jared Boone
License: GNU General Public License, version 2
projects/greatscottgadgets_greatfet_hardware_begonia/current_version/working/working.kicad_sch:
Copyright 2015 Michael Ossmann
License: GPL v2
